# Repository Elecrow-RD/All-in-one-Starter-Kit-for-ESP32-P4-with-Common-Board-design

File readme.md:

### 1, Product picture

### 2, Product version number

|      | Hardware | Software | Remark |
| ---- | -------- | -------- | ------ |
| 1    | V1.0     | V1.0     | old |
| 2    | V1.1     | V1.1     | latest |

Differences between versions:

**V1.0**: This version uses a 360° servo.

**V1.1**: This version uses a 180° servo.

Use the corresponding code in Lesson 8.

### 3, product information

| Main Processor（ESP32-P4）       |                                                              |
| -------------------------------- | ------------------------------------------------------------ |
| CPU/SoC                          | 32-bit RISC-V dual-core processor up to 360 MHz for HP system;32-bit RISC-V single-core processor up to 40 MHz for LP system |
| System Memory                    | 16 MB (OPI/HPI)³  in-Package PSRAM                           |
| Storage                          | 128 KB HP ROM、16 KB LP ROM                                  |
| Development language             | C/C++ Language                                               |
| **Display**                      |                                                              |
| Size                             | 7inch                                                        |
| Resolution                       | 1024*600                                                     |
| Touch Type                       | Capacitive                                                   |
| Panel Type                       | IPS                                                          |
| **Wireless Communication**       |                                                              |
| Bluetooth                        | Not supported                                                |
| WiFi                             | Not supported                                                |
| Wireless communication expansion | Support can be used with [wireless module](https://www.elecrow.com/wireless-module-for-crowpanel-advanced-series.html) |
| Camera                           | 2 MegaPixels,100° wide-angle                                 |
| **Hardware**                     |                                                              |
| Interface                        | 1x TYPE-C Interface,1x I/C(ZX-HY2.0-4PZZ), 1x UART(ZX-HY2.0-4PZZ), 1xI/O(20P*2,P=2.54mm), 1xCSI, 1xUSB, 1x Ethernet,1x TF Card Slot |
| Button                           | Rest Button                                                  |
| LED Indicator                    | I/O port working status indicator light                      |
| **Other**                        |                                                              |
| Size                             | 195\*170*46（mm）                                            |
| Material                         | PP Plastic                                                   |
| Input                            | 5v                                                           |
| Weight                           | 600g                                                         |

### 4, Use the driver module

| Name | dependency library |
| ---- | ------------------ |
| LVGL | lvgl/lvgl@8.3.3    |

### 5,Quick Start
##### Arduino IDE starts

1.Download the library files used by this product to the 'libraries' folder.

C:\Users\Documents\Arduino\libraries\

2.Open the Arduino IDE

3.Open the code configuration environment and burn it

##### ESP-IDF starts

1.Right-click on an empty space in the project folder and select "Open with VS Code" to open the project.

2.In the IDF plug-in, select the port, then compile and flash

### 6,Folder structure.
|--3D file： Contains 3D model files (.stp) for the hardware. These files can be used for visualization, enclosure design, or integration into CAD software.

|--Datasheet: Includes datasheets for components used in the project, providing detailed specifications, electrical characteristics, and pin configurations.

|--Eagle_SCH&PCB: Contains **Eagle CAD** schematic (`.sch`) and PCB layout (`.brd`) files. These are used for circuit design and PCB manufacturing.

|--example: Provides example code and projects to demonstrate how to use the hardware and libraries. These examples help users get started quickly.

|--factory_firmware: Stores pre-compiled factory firmware that can be directly flashed onto the device. This ensures the device runs the default functionality.

|--factory_sourcecode:  Contains the source code for the factory firmware, allowing users to modify and rebuild the firmware as needed.

|--libraries: Includes necessary libraries required for compiling and running the project. These libraries provide drivers and additional functionalities for the hardware.

### 7,Pin definition
1，Ultrasonic Sensor：

2，LIGHT SENSOR

3，LED

4,Temperature & Humidity(DHT20)

5,DSI

6.PIR

IO24；

7.Servo Motor

IO25;

8,Accelerometer & Gyro

9,HALL SENSOR

IO7;

10,Custom key

IO16;

11,Touch Sensor

IO2;

12,MIC

13,Audio Interface

14,GAS-MQ2

IO17;

15,Relay

IO42;

16,CSI Interface

17,Wireless module

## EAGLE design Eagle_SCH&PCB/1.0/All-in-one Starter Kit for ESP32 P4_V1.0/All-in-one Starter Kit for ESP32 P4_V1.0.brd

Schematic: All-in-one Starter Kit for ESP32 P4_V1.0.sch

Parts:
C1, C2, C3, C10, C19, C20, C22, C25, C27, C28, C29, C32, C33, C34, C36, C38, C39, C41, C44, C46, C48, C49, C50, C51, C52, C56, C58, C60, C61, C63, C64, C66, C67, C69, C81, C85, C87, C89, C91, C95, C100, C102, C111, C118, C121, C209: 100nF; 0603
C4, C7: 15pF; 0603
C5, C6: 12pF; 0603
C8: 100nF_NC; 0603
C9, C11, C18, C21, C23, C24, C31, C42, C47, C65, C70, C75, C96, C97, C98, C109, C113, C122: 1uF; 0603
C12, C14, C15, C17, C26, C30, C35, C37, C55, C57, C59, C80, C86, C88, C94, C99, C103, C106, C110, C114, C115, C116: 10uF; 0603
C13, C16: 22pF; 0603
C40, C43: 10nF; 0603
C45, C195, C213: 4.7uF; 0603
C53, C54: 15pF; C0603
C62, C68, C83: 1uF; C0603
C71, C72, C76, C77: 47uF; 0603
C73, C74, C78, C79: 1nF; 0603
C82, C84, C90, C92: 22uF; C0805
C93: 10nF/25V; 0603
C101, C107, C108: 10nF; C0603
C104, C105: 22nF; C0603
C112: 1uF_NC; 0603
C117, C119, C120: 10uF; C0603
C212: 12pF; C0603
C225: 47uF; C0805
D001, D003: NC/H5VL10B; H5VL10B
D002, D019, D063, D064, D065: LESD5D5.0CT1G; TVS_LESD5D5.0CT1G
D004, D007: H5VL10B
D005: 1N4148; D_SOD123
D006: YELLOW; LED-8MM
D008: GREEN; LED-8MM
D009: BLUE; LED-8MM
D010, D021: DSS34_NC; D_SOD123FL
D11: RED; LED-8MM
D012, D013, D014, D015, D017, D018: LMBR140ET1G
D016: MM1W18_18V; LMSZ5233BT1G
D020: LMSZ5233BT1G_-6V; LMSZ5233BT1G
D022: B5819W; SOD-123_MINI-SMA
D023, D024, D025, D026, D027, D028, D029, D030, D031, D032, D033, D034, D035, D036, D037, D038, D039, D040, D041, D042, D043, D044, D045, D046, D047, D048, D049, D050, D051, D052, D053, D054, D055, D056, D057, D058, D059, D060, D061, D062: GREEN; LED_0603_SMT
D066: DSS34; D_SOD123FL
D130: RED; LED_0603_SMT
FB1: 0R/800mA; L0603
FB2, FB3, FB4, FB5: 1K/磁珠; L0603
FB9: FB 220R/MH2012HM221-T; L0805
IC1: W25Q128JVSIQ; SOIC127P790X216-8N
J1: USB2 High Speed & Power in; WZ3532R024-ESP32-V0.1-20221226_KEVIN_3.0TYPEC-SMD
J2: HR913550A; LORA_BASIC_GATEWAY_-MODULE_HR911105A-RJ45
J3: A_XBJ_CONNECTOR_TWIG-4P-2.0-SMD-FEMALE-REINFORCE9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; A_XBJ_CONNECTOR_4P-SMD-2.0-90D
J4: C42605_USB-TypeA; C42605/USB2.0
J5: USB1 & Power in; WZ3532R024-ESP32-V0.1-20221226_KEVIN_3.0TYPEC-SMD
J6: Gas Sensor Socket; MQ2
J7: HOLDER-MICROSD-9P; 9P-SMD-W/-RING
J8, J9: CONN_20; 1X20
J10, J18, J19: TWIG_2.0; 2.0_1X4
J11: L; 1X02L
J12: C262349_15P_1MM_下接_AFA07-S15FCC-00
J13, J16: HEADER-7P-18.28X2.5; H7-2.54-18.28X2.5X5MM
J14: CROWPI_POW_ULTRA
J15: R; 1X02L
J17: C19273935_40P_0.5MM_下接_HC-FPC-0.5-40P-FH20
J20: CON-2.54MM-3P; CON-PZ-2.54MM-1*3P-WT
J21, J22: CONN_01_3.1MM_SMD1X01_3.1MM_SMD; 1X01_2MM
J23, J24: CONN_01_2.6MM1X01_2.6-4MM; 1X01_2.6MM
J101: D203S_C78793; 3P-D8.1MM
J123: 3.5MM3P; 3.5MM*3P
K1, K2: KEY-4.5X4.5; KEY-4.5X4.5-SMD
K4: RELAY-SRD; REY5-6-19.1X15.5X15.3MM
K5, K6, K7, K8: BUTTON_2P
L1, L2: 2.2μH_C5832372; 1008(2520)
L3: NC; L0603
L4, L5, L6: 4.7uH_C45385206_2.4A; 1008(2520)
L7: 10UH; SMD-4X4MM
LED1, LED6: RED; DISCRETE_LED-0603
P1, P2, P3, P4, P5, P6, P7, P8, P9, P10, P11, P12, P13, P14, P15, P16, P17, P18, P19, P20, P21, P22, P23, P24, P25, P26, P27, P28, P29, P30, P31, P32, P33, P34, P35, P36, P37, P38, P39, P40, P41, P42, P43, P44, P45, P46, P47, P48, P49, P50, P51, P52, P54, P55, P56, P57, P58, P59, P60, P61, P62, P63, P64, P65, P66, P67, P68, P69, P70, P71: TEST_PADPAD-1.5MM; TEST_PAD-1.5MM
P101: KEY; 1P-D450
Q1, Q3, Q7: AO3401A; SOT23-3
Q2, Q4: LMBT3906DW1T1G
Q5, Q6, Q106, Q107: BSS138; SOT23
Q115: S9013; SOT23@1
Q405: 2N7002; SOT23
R1, R4, R7, R10, R61, R64, R73, R79, R81, R83, R123: 5.1K; R0603
R2, R3, R5, R8, R9, R15, R17, R19, R20, R30, R31, R34, R35, R37, R39, R40, R41, R42, R43, R44, R45, R46, R47, R48, R49, R50, R51, R52, R53, R54, R55, R58, R59, R60, R63, R68, R69, R70, R71, R74, R75, R76, R77, R78, R88, R118, R119, R120, R133, R140, R141, R144, R145, R151, R176, R185, R186, R187, R188, R189, R190, R196, R197, R199, R200, R203, R205, R206, R211, R212, R213, R214, R215, R216, R217, R219, R220, R221, R222, R225, R227, R228, R230, R231, R232, R289, R290, R291, R292, R293, R294, R295, R296, R297, R298, R302, R305, R311, R312, R313, R315, R317, R324, R328, R332: 0R; R0603
R6: 10M_NC; R0603
R11, R12, R276: 22R; R0603
R13, R14, R16, R18, R22, R24, R25, R38, R94, R95, R107, R109, R112, R113, R115, R117, R146, R149, R161, R162, R164, R177, R178, R179, R182, R191, R194, R201, R237, R273, R283, R286, R288: 10K; R0603
R21, R23, R173, R175: 51K; R0603
R26, R165, R284: 100K; R0603
R27: 22.1K; R0603
R28: 0R/0805; R0805-SP
R29: 13k; R0603
R32, R33, R86, R87, R147, R180, R181, R192, R193, R210, R238: 10K_NC; R0603
R36, R91, R134, R198, R226, R258, R260, R329: 0R_NC; R0603
R56, R62, R92, R106, R169, R209, R287, R639, R652: 1K; R0603
R57, R108, R110: 1M; R0603
R65: 6.2K; R0603
R66: 1.5K_NC; R0603
R67: 1.5K; R0603
R72, R80, R82, R84, R85: 5.1K_NC; R0603
R89, R97, R98, R121, R122, R125, R126, R207, R208, R257, R259, R422, R423: 4.7K; R0603
R90: 0R; R0805-SP
R93, R99, R102: 470R; R0603
R96, R148, R152, R153, R154, R155, R156, R157, R274: 100R; R0603
R100, R101, R223, R224: 4.7K; R0603-SP
R103, R104: 4.7K_NC; R0603
R105: 500K; 3P-SMD-SQUA-3.6X3.3
R111: 1M_1%; R0603
R114: 3.3K; R0603
R116: 130K; R0603
R124: 5.1R; R0603
R127, R128, R129, R131, R132, R160: 10K; R0603-SP
R130: 10K_NC; R0603-SP
R135, R139: 100K; R0603-SP
R136, R137, R138, R170, R171: 0R; R0603-SP
R142: 95.3K; R0603
R143: 50K; R0603-SP
R150: 13K; R0603
R158, R202: 4.02K; R0603
R159: 1.1R; R0603-SP
R163: 1.1R_NC; R0603-SP
R166: 180K; R0603
R167: 12K; R0603
R168: 1.6K; R0603
R172, R174: 220R; R0603
R195: 1K_NC; R0603
R234, R235, R236, R239, R240, R241, R242, R243, R244, R245, R246, R247, R248, R249, R250, R251, R252, R253, R254, R255, R256, R261, R262, R263, R264, R265, R266, R267, R268, R269, R270, R271, R272, R275, R277, R278, R279, R280, R281, R282, R285: 30K; R0603
R299, R307, R653: 2K; R0603
R654: 3.6K; R0603
R655: 8.2K; R0603
SW1, SW2: switch_6pin; SWITCH_6PIN_2P
TP1, TP2, TP3, TP4, TP5, TP6, TP7, TP8, TP9, TP10, TP11, TP12: TPTP08R; TP08R
U1: ESP32-P4NRW32; IC_ESP32-P4NRW32
U2, U3: RY3430_C370755; SOT95P280X145-5N
U4: IP101GR; QFN32_4X4
U5: DHT20; CROWTAIL-DHT20-V1.0-20211013_DHT20
U6: LSM6DS3TR-C; LGA-14L
U7: HAL248; SOT-23W
U8: LMD4737T261; MIC_LMD4737T261
U9: NS4168-L; NS4168-ESOP-8
U10: NS4168-R; NS4168-ESOP-8
U11: MT9201; COOPER_SOT23-6
U12: CH340K; ESOP-10-EP-150MIL
U13: UMH3NTN; SOP65P210X100-6N
U14: WS2814A
U15: ME6211C18M5G-N_NC; SOT95P282X145-5N
U16: SX1308; SOT95P280X145-6N
U17: MT3540; SOT95P280X145-5N
U18: MT3608; DBV_R-PDSO-G6
U19: SGM3799_NC; IC_SGM3799_TQFN2.6X1.8_16L
U44: ETA6280S2F/RY2121; IC_SOT23-5
U101: BIS0001; SOP16
U121: BH1750; B1750
U123: TTP223; SOT23-6L
U$196: MSOP10
Y1: 40MHZ; X322540MPB4SI
Y2: X322525MSB4SI; SMD3225
Y4: 32.768K; NORDIC_NRF_XTAL_3215_N

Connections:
3.3V: J17.2, P34.P$1, R199.2
3V3_MIC: C69.2, FB1.2, R133.1, U8.6 (VDD_6)
+5V_SYS_GAS: C67.2, J6.1 (A), J6.2 (H), J6.3 (A), R126.2, SW1.2 (2_COM2)
AUDIO_VDD_3V3: Q7.3 (3_D), R135.2, R139.2
AVDD33: C55.2, C56.2, R59.1, U4.31 (AVDD33)
BIT_P0.31_HAL: C65.1, P21.P$1, R123.1, R213.1, U7.2 (VOUT)
CLK_N: R186.2, U1.37 (DSI_CLKN)
CLK_P: R185.2, U1.38 (DSI_CLKP)
COL: R79.1, R80.2, U4.4 (COL/RMII)
COM: J123.2, K4.2
CRS: R81.1, R82.2, U4.20 (CRS/LEDMOD)
CSICLK_N: R156.1, U1.45 (CSI_CLKN)
CSICLK_P: R157.1, U1.44 (CSI_CLKP)
CSID0_N: R152.1, U1.42 (CSI_DATAN0)
CSID0_P: R153.1, U1.43 (CSI_DATAP0)
CSID1_N: R154.1, U1.46 (CSI_DATAN1)
CSID1_P: R155.1, U1.47 (CSI_DATAP1)
CSI_3V3: C80.1, C81.1, R144.2, R145.1, R146.1, R147.1
CSI_CLK_N: J12.8, R156.2, TP5.TP
CSI_CLK_P: J12.9, R157.2, TP6.TP
CSI_D0_N: J12.2, R152.2, TP1.TP
CSI_D0_P: J12.3, R153.2, TP2.TP
CSI_D1_N: J12.5, R154.2, TP3.TP
CSI_D1_P: J12.6, R155.2, TP4.TP
DA1: J7.8 (DATA1), P49.P$1, R127.1
DA2: J7.1 (DATA2), P51.P$1, R131.1
DATA0_N: R190.2, U1.40 (DSI_DATAN0)
DATA0_P: R189.2, U1.39 (DSI_DATAP0)
DATA1_N: R188.2, U1.36 (DSI_DATAN1)
DATA1_P: R187.2, U1.35 (DSI_DATAP1)
DN_N: D019.2, J5.A7 (DN1), J5.B7 (DN2), R9.2
DP_P: D064.2, J5.A6 (DP1), J5.B6 (DP2), R8.2
DSI_CLK_N: J17.23, R186.1, TP11.TP
DSI_CLK_P: J17.24, R185.1, TP12.TP
DSI_DATA0_N: J17.17, R190.1, TP7.TP
DSI_DATA0_P: J17.18, R189.1, TP8.TP
DSI_DATA1_N: J17.20, R188.1, TP9.TP
DSI_DATA1_P: J17.21, R187.1, TP10.TP
DTR: R13.2, U12.4 (DTR#), U13.4 (E2)
EN_DCDC: R31.2, U1.79 (EN_DCDC)
ESP_LDO_VO1: C21.2, R37.2, U1.71 (VFB1/VO1)
ESP_LDO_VO2: C24.1, R40.2, U1.72 (VFB2/VO2)
ESP_LDO_VO3: C47.2, R51.2, U1.73 (VFB3/VO3)
ESP_LDO_VO4: C31.2, R44.2, U1.74 (VFB4/VO4)
ESP_VDD_HP_1V2: R34.2, R48.2, R49.2, R50.2
FB_DCDC: C16.1, R32.2, R33.1, R203.1, U3.5 (FB)
FLASH_CK: IC1.6 (CLK), U1.32 (FLASH_CK)
FLASH_CS: IC1.1 (/CS), R38.1, U1.27 (FLASH_CS)
FLASH_D: IC1.5 (DI_(IO0)), U1.33 (FLASH_D)
FLASH_HOLD: IC1.7 (/HOLD_OR_/RESET_(IO3)), U1.31 (FLASH_HOLD)
FLASH_Q: IC1.2 (DO_(IO1)), U1.28 (FLASH_Q)
FLASH_WP: IC1.3 (/WP_(IO2)), U1.29 (FLASH_WP)
GND: C1.2, C2.1, C3.2, C4.2, C5.2, C6.2, C7.1, C8.2, C9.1, C10.1, C11.1, C12.2, C14.1, C15.2, C17.1, C18.2, C19.1, C20.2, C21.1, C22.2, C23.2, C24.2, C25.2, C26.1, C27.2, C28.2, C29.2, C30.1, C31.1, C32.2, C33.2, C34.2, C35.1, C36.2, C37.1, C38.2, C39.2, C40.2, C41.2, C42.2, C43.2, C44.2, C45.2, C46.2, C47.1, C48.2, C49.2, C50.1, C51.1, C52.1, C53.2, C54.1, C55.1, C56.1, C57.1, C58.1, C59.1, C60.1, C61.1, C62.1, C63.1, C64.1, C65.2, C66.1, C67.1, C68.1, C69.1, C70.2, C71.2, C72.2, C73.1, C74.1, C75.2, C76.2, C77.2, C78.1, C79.1, C80.2, C81.2, C82.2, C83.1, C84.2, C85.1, C86.2, C87.2, C88.2, C89.2, C90.2, C91.2, C92.2, C94.2, C95.2, C98.2, C99.2, C100.2, C101.1, C102.1, C106.1, C107.2, C108.2, C109.2, C110.2, C111.2, C112.2, C113.2, C114.1, C115.2, C116.2, C117.1, C118.1, C119.1, C120.1, C121.1, C122.1, C195.2, C209.1, C212.1, C213.1, C225.1, D001.1, D002.1, D003.1, D004.2, D007.2, D016.2, D018.1, D019.1, D020.1, D063.1, D064.1, D065.1, IC1.4 (GND), J1.A1 (GND), J1.A12 (GND), J1.B1 (GND), J1.B12 (GND), J1.P$9, J1.P$10, J1.P$11, J1.P$12, J3.4, J3.SS1, J3.SS2, J4.1 (1.GND), J4.5, J4.6, J5.A1 (GND), J5.A12 (GND), J5.B1 (GND), J5.B12 (GND), J5.P$9, J5.P$10, J5.P$11, J5.P$12, J7.6 (VSS), J7.G1, J7.G2, J7.G3, J7.G4, J8.4, J8.5, J8.6, J8.13, J8.17, J8.20, J9.16, J9.17, J9.20, J10.1, J11.3, J11.4, J12.1, J12.4, J12.7, J12.10, J12.16, J12.17, J13.6, J13.6-6 (6), J14.P$1 (1_GND), J15.3, J15.4, J17.3, J17.7, J17.8, J17.9, J17.10, J17.16, J17.19, J17.22, J17.25, J17.28, J17.31, J17.41, J17.42, J18.1, J19.1, J20.3 (S), J21.1, J22.1, J23.1, J24.1, J101.3 (G), K1.1, K2.2, K5.P$1, K6.P$1, K7.P$1, K8.P$1, LED6.-, P20.P$1, P28.P$1, P29.P$1, P31.P$1, P65.P$1, Q115.2 (E), R1.2, R4.1, R7.2, R10.1, R21.1, R22.1, R23.1, R24.1, R27.2, R29.2, R33.2, R57.1, R62.2, R64.2, R65.2, R73.1, R80.1, R82.1, R84.1, R87.1, R91.1, R107.1, R108.1, R119.1, R120.1, R124.1, R125.2, R132.2, R134.1, R143.1, R150.2, R158.2, R159.1, R160.2, R162.1, R163.1, R167.1, R169.1, R173.1, R175.1, R180.1, R182.1, R192.1, R194.1, R202.1, R234.2, R238.1, R252.2, R256.2, R261.2, R262.2, R263.2, R264.2, R265.2, R266.2, R267.2, R268.2, R269.2, R270.2, R271.2, R272.2, R273.1, R275.2, R277.2, R278.2, R279.2, R280.2, R281.2, R282.2, R285.1, R286.2, R288.2, R307.2, SW2.4 (4_1A), U1.105 (GND), U2.2 (GND), U3.2 (GND), U4.EXP (PAD), U5.3 (GND), U6.6 (GND), U6.7 (GND), U7.3 (GND), U8.1 (GND_1), U8.3 (GND_3), U9.7 (GND), U9.9 (PE), U10.7 (GND), U10.9 (PE), U11.2 (2-GND), U12.3 (GND), U12.EP, U14.4 (GND), U15.2 (VSS), U16.2 (2_GND), U17.2 (2_GND), U18.2 (GND), U19.6 (6_GND), U44.2 (2_GND), U101.7 (VSS), U121.3 (GND\), U123.2 (GND), U$196.5 (GND), Y1.2 (GND_1), Y1.4 (GND_2), Y2.2 (GND), Y2.4 (GND)
IN1: C212.2, P101.1, U123.3 (IN)
INT1: P22.P$1, U6.4 (INT1)
INT2: P23.P$1, U6.9 (INT2)
INT_TP: J17.4, P35.P$1, R227.2
IO2: U1.2 (GPIO2), U19.4 (4_COM2), U$196.3 (CO+)
IO2_CLK: J16.3, J16.3-3 (3), P45.P$1, R177.1, U19.3 (3_NO2), U$196.9 (L1+)
IO2_RTS: P18.P$1, R287.2, U19.5 (5_NC2), U$196.7 (L0+)
IO3_MIC_CLK: U1.3 (GPIO3), U8.4 (CLK_4)
IO4_MIC_DATA: U1.4 (GPIO4), U8.5 (DATA_5)
IO5_RESET_LCD: R151.1, R231.2, U1.5 (GPIO5)
IO6_AUDIO_EN: Q7.1 (1_G), R95.1, R294.1, U1.6 (GPIO6)
IO7: R315.2, U1.7 (GPIO7), U19.8 (8_COM3), U$196.4 (CO-)
IO7_CMD: J16.2, J16.2-2 (2), P44.P$1, R178.1, U19.7 (7_NO3), U$196.8 (L1-)
IO7_HALL: R213.2, U19.9 (9_NC3), U$196.6 (L0-)
IO8_LED: P32.P$1, R148.1, R290.2, U1.8 (GPIO8)
IO9: R220.2, R291.2, U1.10 (GPIO9)
IO9_W_CLK: J13.2, J13.2-2 (2), P27.P$1, R220.1
IO10: R221.2, R295.2, U1.11 (GPIO10)
IO10_W_MISO: J13.3, J13.3-3 (3), P26.P$1, R221.1
IO11: R222.2, R296.2, U1.12 (GPIO11)
IO11_W_MOSI: J13.4, J13.4-4 (4), P25.P$1, R222.1
IO12_US_ECHO: R299.2, U1.13 (GPIO12)
IO13_US_TRIG: R212.2, U1.14 (GPIO13)
IO14: R219.2, R324.2, U1.15 (GPIO14)
IO14_W_BUSY: J16.6, J16.6-6 (6), P40.P$1, R219.1
IO15: R5.2, R302.1, U1.16 (GPIO15)
IO15_W: J16.5, J16.5-5 (5), P41.P$1, R5.1
IO16_ADC_KEY: P16.P$1, R214.2, R639.2, R652.2, R653.2, R654.2, R655.2
IO17_ADC_MQ2: J6.4 (B), J6.6 (B), P17.P$1, R125.1, R215.2
IO18_I2C1_SDA: J17.5, P36.P$1, Q107.2 (S), R103.2, R205.2, R208.2, R260.1, U5.2 (SDA), U6.14 (SDA), U121.4 (SDA)
IO18_SDA: J10.3, J18.3, Q107.3 (D), R259.2, R260.2
IO19_I2C1_SCL: J17.6, P37.P$1, Q106.2 (S), R104.2, R206.2, R207.2, R258.1, U5.4 (SCL), U6.13 (SCL), U121.6 (SCL)
IO19_SCL: J10.4, J18.4, Q106.3 (D), R257.2, R258.2
IO20_LED_BK_EN: R160.1, R232.2, U11.4 (4-EN)
IO21_I2S_LRCLK: R136.2, U1.23 (GPIO21)
IO22_I2S_BCLK: R137.2, U1.24 (GPIO22)
IO23_I2S_DSDIN: R138.2, U1.25 (GPIO23)
IO24_PIR: P30.P$1, R112.1, U1.52 (GPIO24)
IO25_SERVO: Q405.2 (S), R211.2, R329.2, R422.1
IO32_UPDN: R230.1, U1.63 (GPIO32)
IO33_SHLR: R225.1, U1.64 (GPIO33)
IO35_BOOT: C8.1, K2.1, R17.1, R18.1, R70.2, U13.3 (C2)
IO36: R94.2, U1.68 (GPIO36)
IO39_SD_DO: J7.7 (DO), P6.P$1, R128.1, R332.2
IO40_RESET_TP: R228.1, U1.81 (GPIO40)
IO41_INT_TP: R227.1, R317.2, U1.82 (GPIO41)
IO42_RELAY: P58.P$1, R274.2, U1.83 (GPIO42)
IO43_SD_SCK: J7.5 (SCLK), P7.P$1, R217.2
IO44_SD_CMD: J7.3 (DI), P8.P$1, R129.1, R216.2
IO45_I2C2_SDA: J12.14, P69.P$1, R98.2, R313.2, U1.87 (GPIO45)
IO46_I2C2_SCL: J12.13, P68.P$1, R97.2, R312.2, U1.88 (GPIO46)
IO47_TX: J19.3, Q5.3 (D), R223.2
IO47_UART_TX: Q5.2 (S), R224.2, R297.2, U1.89 (GPIO47)
IO48_RX: J19.4, Q6.3 (D), R101.2
IO48_UART_RX: Q6.2 (S), R100.2, R298.2, U1.90 (GPIO48)
IO53_W_TX_CE: R171.2, R328.2, U1.97 (GPIO53)
IO54_W_RX_IRQ: R170.2, R305.1, U1.98 (GPIO54)
IO-5: J9.13, R231.1, R247.2
IO-6: J9.12, R246.2, R294.2
IO-7: J9.10, R244.2, R315.1
IO-8: J9.11, R245.2, R290.1
IO-9: J9.6, R240.2, R291.1
IO-10: J9.5, R239.2, R295.1
IO-11: J9.4, R236.2, R296.1
IO-14: J9.3, R235.2, R324.1
IO-15: J9.9, R243.2, R302.2
IO-26: J9.15, R249.2, R293.2
IO-27: J9.14, R248.2, R292.2
IO-41: J8.14, R253.2, R317.1
IO-45: J8.18, R254.2, R313.1
IO-46: J8.19, R255.2, R312.1
IO-47: J9.18, R250.2, R297.1
IO-48: J9.19, R251.2, R298.1
IO-53: J9.7, R241.2, R328.1
IO-54: J9.8, R242.2, R305.2
IOT_5V: J13.7, J13.7-7 (7), L3.1
IO_DO_N: R12.1, U1.69 (GPIO37)
IO_DO_P: R11.1, U1.70 (GPIO38)
LCD_3V3: R195.2, R199.1, R200.2, R201.2
LCD_AVDD_9V6: C92.1, C93.1, D013.1, D014.2, J17.32, P14.P$1, R166.2, R168.2
LCD_VCOM_3V3: C94.1, C95.1, P15.P$1, R168.1, R169.2, R197.1, R198.1
LCD_VDD_1V8: C88.1, C89.1, P10.P$1, R141.2, R179.2, R181.2, R191.2, R193.2, R196.1, U15.5 (VOUT)
LCD_VGH_18V: C99.1, C100.1, D016.1, J17.38, P12.P$1, R172.1, R173.2
LCD_VGL_-6V: C110.1, C111.1, D020.2, J17.37, P11.P$1, R174.1, R175.2
LED+: C84.1, C85.2, D010.-, D012.1, P63.P$1, R176.1, U11.5 (5-OV)
LED-: J17.33, J17.34, P64.P$1, R159.2, R163.2, U11.3 (3-FB)
unnamed: Q3.1 (1_G), Q4.3 (C1), R23.2
unnamed: C6.1, R6.1, U1.1 (GPIO1), Y4.2
unnamed: C5.1, R6.2, U1.104 (GPIO0), Y4.1
unnamed: Q1.1 (1_G), Q2.3 (C1), R21.2
unnamed: Q2.2 (B2), Q2.5 (B1), Q2.6 (C2), R22.2
unnamed: C43.1, C44.1, C45.1, C46.1, R52.1, U1.51 (VCCA)
unnamed: Q4.2 (B2), Q4.5 (B1), Q4.6 (C2), R24.2
unnamed: J1.B5 (CC2), R4.2
unnamed: J1.A5 (CC1), R1.1
unnamed: J5.A5 (CC1), R7.1
unnamed: R12.2, U12.9 (RXD)
unnamed: R11.2, U12.8 (TXD)
unnamed: R13.1, U13.2 (B1)
unnamed: R15.1, U1.103 (CHIP_PU)
unnamed: R14.1, U13.5 (B2)
unnamed: R17.2, U1.66 (GPIO35)
unnamed: D130.2 (2_K), R307.1
unnamed: R209.1, U44.4 (4_EN)
unnamed: J2.12 (YLED+), R55.1
unnamed: R25.1, U2.1 (EN)
unnamed: L1.1, U2.3 (SW)
unnamed: C13.2, C14.2, L1.2, P2.P$1, R26.1, R28.1
unnamed: C13.1, R26.2, R27.1, U2.5 (FB)
unnamed: R31.1, R210.2, U3.1 (EN)
unnamed: L2.1, U3.3 (SW)
unnamed: C16.2, C17.2, L2.2, P3.P$1, R32.1, R34.1
unnamed: R203.2, U1.78 (FB_DCDC)
unnamed: C15.1, R35.1, R210.1, U3.4 (VIN)
unnamed: C32.1, R45.1, U1.96 (VDDPST_6)
unnamed: J2.11 (YLED-), R56.1
unnamed: J2.7 (NC1), J2.8 (NC2), J2.M1 (SHIELD1), J2.M2 (SHIELD2), R57.2
unnamed: C50.2, J2.4 (TCT)
unnamed: R74.2, U1.92 (GPIO49)
unnamed: C51.2, J2.5 (RCT)
unnamed: R75.2, U1.93 (GPIO50)
unnamed: R77.2, U1.58 (GPIO29)
unnamed: R85.1, U4.24 (TEST_ON)
unnamed: R76.2, U1.60 (GPIO30)
unnamed: R71.2, U1.65 (GPIO34)
unnamed: R78.2, U1.57 (GPIO28)
unnamed: R88.2, U1.94 (GPIO51)
unnamed: J2.10 (GLED-), R62.1
unnamed: J2.9 (GLED+), R63.1
unnamed: R68.2, U1.61 (GPIO31)
unnamed: LED1.+, R89.1
unnamed: J14.P$3 (3_TRIG), R212.1
unnamed: R232.1, U1.22 (GPIO20)
unnamed: R214.1, U1.17 (GPIO16)
unnamed: C209.2, R113.1, U121.5 (DVI)
unnamed: R91.2, U14.5 (5_DOUT)
unnamed: R69.2, U1.95 (GPIO52)
unnamed: D009.2 (C), U14.3 (3_OUTB)
unnamed: D11.1 (A), R93.2
unnamed: R65.1, U4.25 (ISET)
unnamed: D008.2 (C), U14.2 (2_OUTG)
unnamed: D11.2 (C), U14.1 (1_OUTR)
unnamed: R29.1, U44.3 (3_SET)
unnamed: D006.1 (A), R96.2
unnamed: J5.B5 (CC2), R10.2
unnamed: D006.2 (C), U14.8 (8_OUTW)
unnamed: R142.2, R150.1, U18.3 (FB)
unnamed: D008.1 (A), R99.2
unnamed: R92.2, U14.7 (7_VDD)
unnamed: D022.A, L7.2, U18.1 (SW)
unnamed: D009.1 (A), R102.2
unnamed: R117.1, U101.3 (RR1)
unnamed: C108.1, R117.2, U101.4 (RC1)
unnamed: R112.2, U101.2 (VO)
unnamed: R110.2, U101.6 (RR2)
unnamed: C107.1, R110.1, U101.5 (RC2)
unnamed: C104.2, R105.2 (3), R105.3 (2), U101.12 (2OUT)
unnamed: C104.1, R106.2, R116.2, U101.13 (2IN-)
unnamed: R109.2, U101.9 (VC)
unnamed: R108.2, U101.10 (IB)
unnamed: C101.2, J101.2 (S), R107.2, R118.2
unnamed: C103.2, C105.1, R111.1, U101.16 (1OUT)
unnamed: C105.2, R111.2, R114.2, U101.15 (1IN-)
unnamed: C103.1, R106.1
unnamed: C225.2, R114.1
unnamed: R115.2, U101.1 (A)
unnamed: R118.1, U101.14 (1IN+)
unnamed: R105.1, R116.1
unnamed: R119.2, U6.2 (SDX)
unnamed: R120.2, U6.3 (SCX)
unnamed: R121.2, U6.12 (CS)
unnamed: R122.2, U6.1 (SDO)
unnamed: J6.5 (H), R124.2
unnamed: LED6.+, R126.1
unnamed: R217.1, U1.84 (GPIO43)
unnamed: R216.1, U1.86 (GPIO44)
unnamed: R133.2, R134.2, U8.2 (L/R_2)
unnamed: R135.1, U10.1 (CTRL)
unnamed: P61.P$1, R136.1, U9.2 (LRCLK), U10.2 (LRCLK)
unnamed: P60.P$1, R137.1, U9.3 (BCLK), U10.3 (BCLK)
unnamed: P59.P$1, R138.1, U9.4 (SDATA), U10.4 (SDATA)
unnamed: FB2.1, U10.8 (VOP)
unnamed: FB3.1, U10.5 (VON)
unnamed: R332.1, U1.80 (GPIO39)
unnamed: C78.2, FB4.2, J11.2, P54.P$1
unnamed: R139.1, R143.2, U9.1 (CTRL)
unnamed: C97.2, D017.1, D018.2
unnamed: R162.2, U$196.10 (EN)
unnamed: FB4.1, U9.8 (VOP)
unnamed: FB5.1, U9.5 (VON)
unnamed: C79.2, FB5.2, J11.1, P55.P$1
unnamed: C74.2, FB3.2, J15.1, P57.P$1
unnamed: J12.15, P70.P$1, R145.2
unnamed: J12.11, P66.P$1, R146.2
unnamed: J12.12, P67.P$1, R147.2
unnamed: R158.1, U1.48 (CSI_REXT)
unnamed: D010.+, D012.2, L5.2, U11.1 (1-SW)
unnamed: C96.1, C97.1, D013.2, L4.2, U16.1 (1_SW)
unnamed: R164.2, U15.3 (CE)
unnamed: R165.2, U16.4 (4_EN)
unnamed: C96.2, D014.1, D015.2
unnamed: C93.2, R166.1, R167.2, U16.3 (3_FB)
unnamed: J13.1, J13.1-1 (1), P43.P$1, R171.1
unnamed: J16.1, J16.1-1 (1), P42.P$1, R170.1
unnamed: C98.1, D015.1, R172.2
unnamed: C109.1, D017.2, R174.2
unnamed: J17.39, J17.40, R176.2
unnamed: R205.1, U1.19 (GPIO18)
unnamed: R206.1, U1.20 (GPIO19)
unnamed: C73.2, FB2.2, J15.2, P56.P$1
unnamed: R211.1, U1.53 (GPIO25)
unnamed: J17.12, J17.13, R196.2, R198.2
unnamed: J17.11, R197.2
unnamed: R202.2, U1.34 (DSI_REXT)
unnamed: R215.1, U1.18 (GPIO17)
unnamed: D023.2 (2_K), R234.1
unnamed: D024.2 (2_K), R235.1
unnamed: D025.2 (2_K), R236.1
unnamed: D026.2 (2_K), R239.1
unnamed: D027.2 (2_K), R240.1
unnamed: K8.P$2, R652.1
unnamed: D028.2 (2_K), R241.1
unnamed: K7.P$2, R653.1
unnamed: K6.P$2, R654.1
unnamed: D029.2 (2_K), R242.1
unnamed: D030.2 (2_K), R243.1
unnamed: K5.P$2, R655.1
unnamed: D031.2 (2_K), R244.1
unnamed: D032.2 (2_K), R245.1
unnamed: D033.2 (2_K), R246.1
unnamed: D034.2 (2_K), R247.1
unnamed: D035.2 (2_K), R248.1
unnamed: D036.2 (2_K), R249.1
unnamed: D037.2 (2_K), R250.1
unnamed: D038.2 (2_K), R251.1
unnamed: D039.2 (2_K), R252.1
unnamed: D040.2 (2_K), R253.1
unnamed: D041.2 (2_K), R254.1
unnamed: D042.2 (2_K), R255.1
unnamed: D043.2 (2_K), R256.1
unnamed: D044.2 (2_K), R261.1
unnamed: D045.2 (2_K), R262.1
unnamed: D046.2 (2_K), R263.1
unnamed: D047.2 (2_K), R264.1
unnamed: D048.2 (2_K), R265.1
unnamed: D049.2 (2_K), R266.1
unnamed: D050.2 (2_K), R267.1
unnamed: D051.2 (2_K), R268.1
unnamed: D052.2 (2_K), R269.1
unnamed: D053.2 (2_K), R270.1
unnamed: D054.2 (2_K), R271.1
unnamed: D055.2 (2_K), R272.1
unnamed: D056.2 (2_K), R275.1
unnamed: D057.2 (2_K), R277.1
unnamed: D058.2 (2_K), R278.1
unnamed: D059.2 (2_K), R279.1
unnamed: D060.2 (2_K), R280.1
unnamed: D061.2 (2_K), R281.1
unnamed: D062.2 (2_K), R282.1
unnamed: R148.2, U14.6 (6_DIN)
unnamed: R149.2, U101.8 (!RESET)
unnamed: R283.2, U17.4 (4_EN)
unnamed: D066.+, L6.2, U17.1 (1_SW)
unnamed: J9.1, J9.2, R289.2
unnamed: R284.1, R285.2, U17.3 (3_FB)
unnamed: J8.1, J8.2, J8.3, R311.1
unnamed: R237.1, R238.2, U121.2 (ADDR)
unnamed: Q115.1 (B), R273.2, R274.1
unnamed: R288.1, U123.4 (AHLB), U123.6 (TOG)
unnamed: R286.1, R287.1, U123.1 (OUT)
unnamed: J14.P$2 (2_ECHO), R299.1
NC: J123.1, K4.4
NO: J123.3, K4.5
PHY_3V3: R55.2, R58.2, R59.2, R60.2, R61.2, R66.2, R67.2, R72.2, R79.2, R81.2, R83.2, R85.2, R86.2
PHY_AD0: R56.2, R61.1, U4.11 (LED0/PHY_AD0)
PHY_AD3: R63.2, R64.1, U4.12 (LED3/PHY_AD3)
PHY_CLK_IO50: R75.1, U4.10 (TXCLK/50M_CLKI), U4.14 (RXCLK/50M_CLKO)
PHY_MDC_IO31: R66.1, R68.1, U4.22 (MDC)
PHY_MDIO_IO52: R67.1, R69.1, U4.23 (MDIO)
PHY_RSTN_IO51: R86.1, R87.2, R88.1, U4.32 (RESET_N)
PHY_RXD0_IO29: R77.1, U4.18 (RXD0)
PHY_RXD1_IO30: R76.1, U4.17 (RXD1)
PHY_RXDV_IO28: R78.1, U4.19 (RXDV/CRS_DV)
PHY_TXD0_IO34: R71.1, U4.9 (TXD0)
PHY_TXD1_IO35: R70.1, U4.8 (TXD1)
PHY_TXEN_IO49: R74.1, U4.5 (TXEN)
REGOUT: C59.2, C60.2, U4.28 (REGOUT)
RESET_LCD: C112.1, J17.14, P38.P$1, R151.2, R193.1, R194.2, R195.1, R226.2
RESET_TP: C113.1, J17.1, P33.P$1, R201.1, R228.2
RST_EN: C3.1, K1.2, R15.2, R16.1, R226.1, U13.6 (C1)
RTS: R14.2, U12.6 (RTS#), U13.1 (E1)
RXER: R83.1, R84.2, U4.21 (RXER/INTR_32)
RX_N: J2.6 (RD-), U4.26 (MDI_RN)
RX_P: J2.3 (RD+), U4.27 (MDI_RP)
SDCS: J7.2 (CS), P50.P$1, R130.1, R132.1
SEL: P48.P$1, R161.1, SW2.5 (5_COM1), U19.2 (2_IN1_2), U19.10 (10_IN3_4), U$196.2 (SEL)
SERVO: J3.1, J20.1 (G), P71.P$1, Q405.3 (D), R329.1, R423.2
SHLR: J17.35, P46.P$1, R181.1, R182.2, R225.2
STBYB: J17.15, P39.P$1, R191.1, R192.2
TXER: R72.1, R73.2, U4.1 (TXER/FXSD)
TX_N: J2.2 (TD-), U4.29 (MDI_TN)
TX_P: J2.1 (TD+), U4.30 (MDI_TP)
UPDN: J17.36, P47.P$1, R179.1, R180.2, R230.2
USB1_5V: C9.2, D063.2, J5.A4 (VBUS), J5.A9 (VBUS), J5.B4 (VBUS), J5.B9 (VBUS), P4.P$1, Q1.3 (3_D), Q2.1 (E2)
USB1_D_N: R9.1, U12.2 (UD-)
USB1_D_P: R8.1, U12.1 (UD+)
USB2_5V: C11.2, D002.2, J1.A4 (VBUS), J1.A9 (VBUS), J1.B4 (VBUS), J1.B9 (VBUS), P5.P$1, Q3.3 (3_D), Q4.1 (E2)
USB2_D_N: D004.1, J1.A7 (DN1), J1.B7 (DN2), R3.2
USB2_D_P: D007.1, J1.A6 (DP1), J1.B6 (DP2), R2.2
USB2_N: D001.2, J4.3 (3.D-), R20.2
USB2_P: D003.2, J4.2 (2.D+), R19.2
USBD_N: R20.1, U1.49 (DM)
USBD_P: R19.1, U1.50 (DP)
USB_5V: C12.1, C106.2, L6.1, P1.P$1, Q1.2 (2_S), Q2.4 (E1), Q3.2 (2_S), Q4.4 (E1), R25.2, R90.1, R283.1, U2.4 (VIN), U17.5 (5_VIN)
USB_A_N: R3.1, R293.1, U1.55 (GPIO26)
USB_A_P: R2.1, R292.1, U1.56 (GPIO27)
V+: K4.1, R276.2
V-: D005.+, K4.3, LED1.-, Q115.3 (C)
VBAT: C49.1, C115.1, R54.1, U1.102 (VBAT)
VBUS_OUT: C116.1, D065.2, J4.4 (4.VCC), P9.P$1, U44.1 (1_OUT)
VCC_5V_SERVO: C119.2, C120.2, C121.2, D021.-, D022.C, J3.3, J20.2 (V), P52.P$1, R142.1, R423.1
VCC_RELAY: C61.2, D005.-, FB9.1, R89.2, R276.1
VDDA: C48.1, R53.1, U1.101 (VDDA)
VDDPST: C22.1, C23.1, R40.1, U1.59 (VDDPST), U1.67 (VDDPST)
VDDPST_1: C25.1, C26.2, R41.1, U1.9 (VDDPST_1)
VDDPST_2: C27.1, R42.1, U1.21 (VDDPST_2)
VDDPST_3: C18.1, C19.2, R36.1, R37.1, R39.1, U1.30 (VDDPST_3)
VDDPST_4: C28.1, R43.1, U1.62 (VDDPST_4)
VDDPST_5: C29.1, C30.2, R44.1, U1.85 (VDDPST_5)
VDDPST_DCDC: C34.1, C35.2, R47.1, U1.77 (VDDPST_DCDC)
VDDPST_LDO: C33.1, R46.1, U1.75 (VDDPST_LDO)
VDD_3V3: C1.1, C2.2, C62.2, C63.2, C64.2, C66.2, C68.2, C70.1, C71.1, C72.1, C75.1, C76.1, C77.1, C102.2, C122.2, C213.2, D023.1 (1_A), D024.1 (1_A), D025.1 (1_A), D026.1 (1_A), D027.1 (1_A), D028.1 (1_A), D029.1 (1_A), D030.1 (1_A), D031.1 (1_A), D032.1 (1_A), D033.1 (1_A), D034.1 (1_A), D035.1 (1_A), D036.1 (1_A), D037.1 (1_A), D038.1 (1_A), D039.1 (1_A), D040.1 (1_A), D041.1 (1_A), D042.1 (1_A), D043.1 (1_A), D044.1 (1_A), D045.1 (1_A), D046.1 (1_A), D047.1 (1_A), D048.1 (1_A), D049.1 (1_A), D050.1 (1_A), D051.1 (1_A), D052.1 (1_A), D053.1 (1_A), D054.1 (1_A), D055.1 (1_A), D056.1 (1_A), D057.1 (1_A), D058.1 (1_A), D059.1 (1_A), D060.1 (1_A), D061.1 (1_A), D062.1 (1_A), FB1.1, J7.4 (VDD), J13.5, J13.5-5 (5), J101.1 (D), P13.P$1, P19.P$1, P24.P$1, Q5.1 (G), Q6.1 (G), Q7.2 (2_S), Q106.1 (G), Q107.1 (G), Q405.1 (G), R28.2, R30.1, R58.1, R95.2, R97.1, R98.1, R100.1, R103.1, R104.1, R109.1, R113.2, R115.1, R121.1, R122.1, R123.2, R127.2, R128.2, R129.2, R130.2, R131.2, R140.1, R141.1, R144.1, R149.1, R161.2, R177.2, R178.2, R200.1, R207.1, R208.1, R224.1, R237.2, R311.2, R422.2, R639.1, U5.1 (VCC), U6.5 (VDDIO), U6.8 (VDD), U7.1 (VCC), U9.6 (VDD), U10.6 (VDD), U12.7 (VCC), U12.10 (V3), U19.14 (14_VCC), U101.11 (VDD), U121.1 (VCC), U123.5 (VCC), U$196.1 (VCC)
VDD_5V: C10.2, C52.2, C82.1, C83.2, C86.1, C87.1, C90.1, C91.1, C117.2, C118.2, D021.+, D130.1 (1_A), FB9.2, J10.2, J14.P$4 (4VCC), J18.2, J19.2, L3.2, L4.1, L5.1, L7.1, R35.2, R90.2, R92.1, R93.1, R96.1, R99.1, R101.1, R102.1, R164.1, R165.1, R223.1, R257.1, R259.1, R289.1, SW1.3 (3_2A), U11.6 (6-VIN), U15.1 (VIN), U16.5 (5_IN), U18.4 (EN), U18.5 (IN)
VDD_5V2: C114.2, C195.1, D066.-, P62.P$1, R209.2, R284.2, U44.5 (5_VIN)
VDD_ESP32: R18.2, R30.2, R43.2, R46.2, R47.2, R52.2, R94.1
VDD_ESP32_1: R16.2, R36.2, R41.2, R42.2, R45.2, R53.2, R54.2, R140.2
VDD_FLASH: C20.1, IC1.8 (VCC), R38.2, R39.2
VDD_HP_0: C36.1, C37.2, R48.1, U1.26 (VDD_HP_0)
VDD_HP_2: C38.1, R49.1, U1.76 (VDD_HP_2)
VDD_HP_3: C39.1, R50.1, U1.91 (VDD_HP_3)
VDD_IO: C57.2, C58.2, R60.1, U4.13 (VDD_IO)
VDD_MIPI_DPHY: C40.1, C41.1, C42.1, R51.1, U1.41 (VDD_MIPI_DPHY)
XIN: C53.1, U4.3 (X2), Y2.1 (XIN)
XOUT: C54.2, U4.2 (X1), Y2.3 (XOUT)
XTAL_N: C7.2, U1.99 (XTAL_N), Y1.3 (CRYSTAL_2)
XTAL_P: C4.1, U1.100 (XTAL_P), Y1.1 (CRYSTAL_1)

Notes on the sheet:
I=6.8/R
Limit current 520mA
ESP32-P4
USB_TypeC *2 & TypeA
DC-DC:5V to 3V3
DC-DC:3V3 to 1V2
ESP32-P4_POWER
USB to UART
POWER
PHY
TypeA Limit Current
Relay
Ultrasonic Sensor
LIGHT SENSOR
I2C
ADD:0X5C
2.7V-4.2V
ADDRESS:0x5C
ADDRESS:1011100
LED
Temperature & Humidity(DHT20)
3V-5.5V
ADDRESS:0X38
PIR
Servo Motor
Accelerometer & Gyro
ADD:0X6B
HALL SENSOR
Custom_key
TTP223
Touch Sensor
GAS-MQ2
开关控制热释电功能的开启或关闭
SD card
MIC
Audio_Interface
CSI_Interface
I led=200mV/1.1=182mA
DSI_LED Driver
LDO:5V/3.3V to 1V8

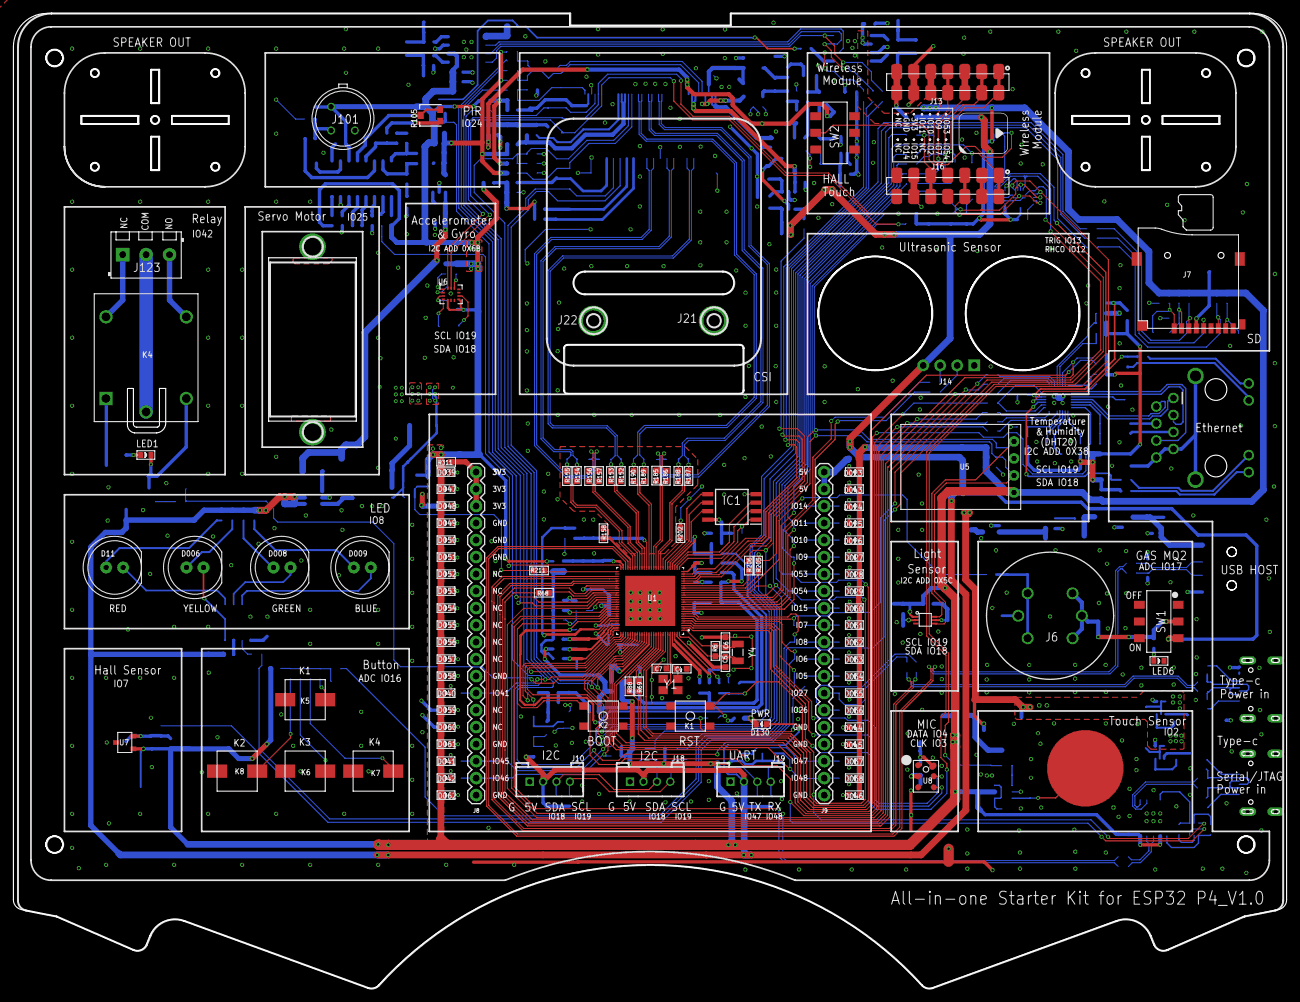
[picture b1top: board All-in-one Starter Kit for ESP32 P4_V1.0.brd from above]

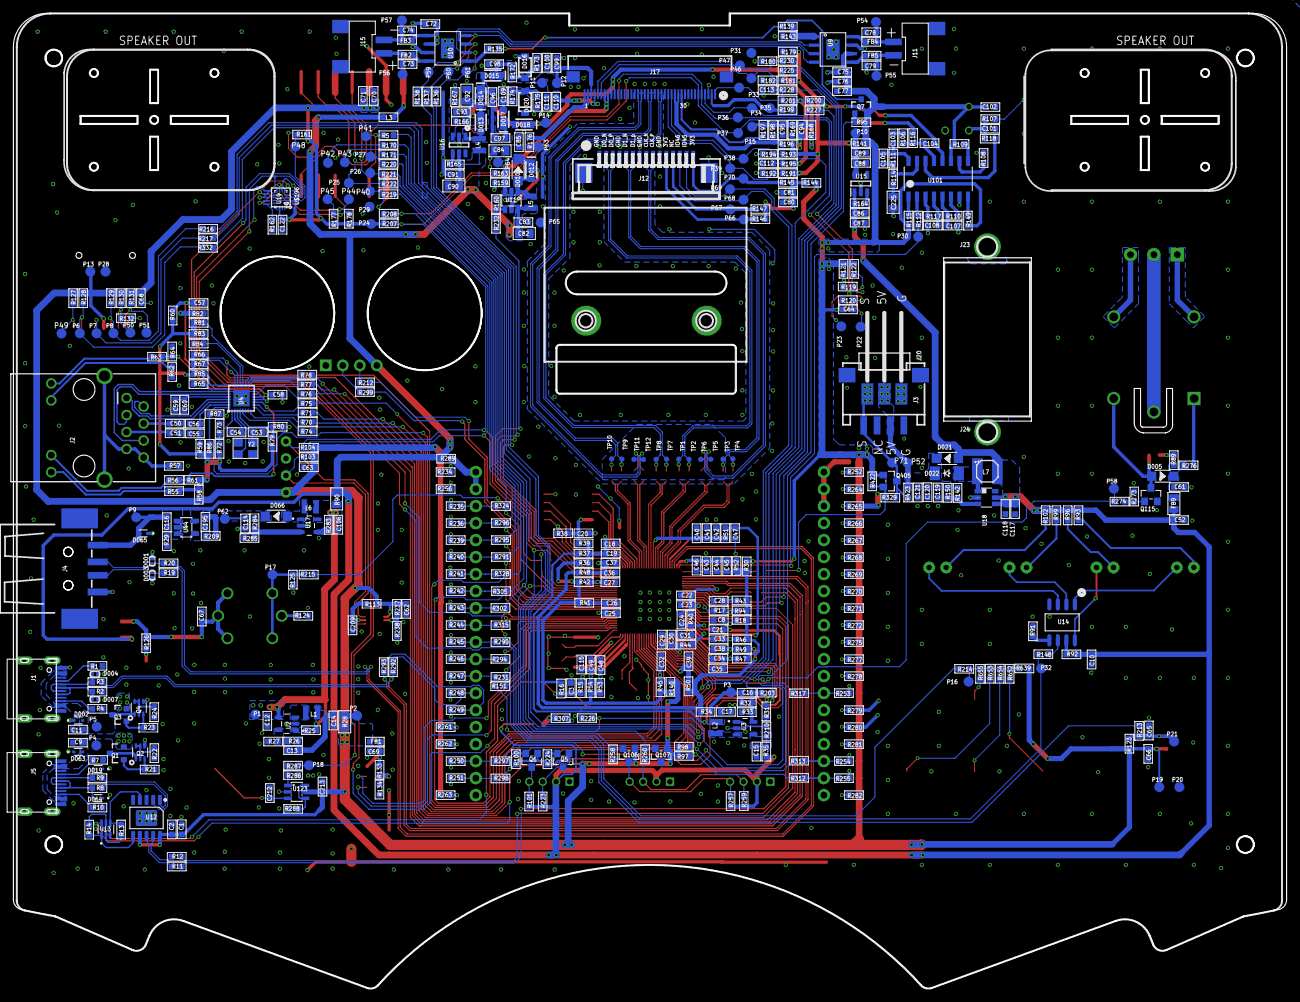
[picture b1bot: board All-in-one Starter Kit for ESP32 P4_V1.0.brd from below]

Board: 2 copper layers, 190.2 x 145.7 mm, 678 parts (571 on the bottom side), 399 nets.

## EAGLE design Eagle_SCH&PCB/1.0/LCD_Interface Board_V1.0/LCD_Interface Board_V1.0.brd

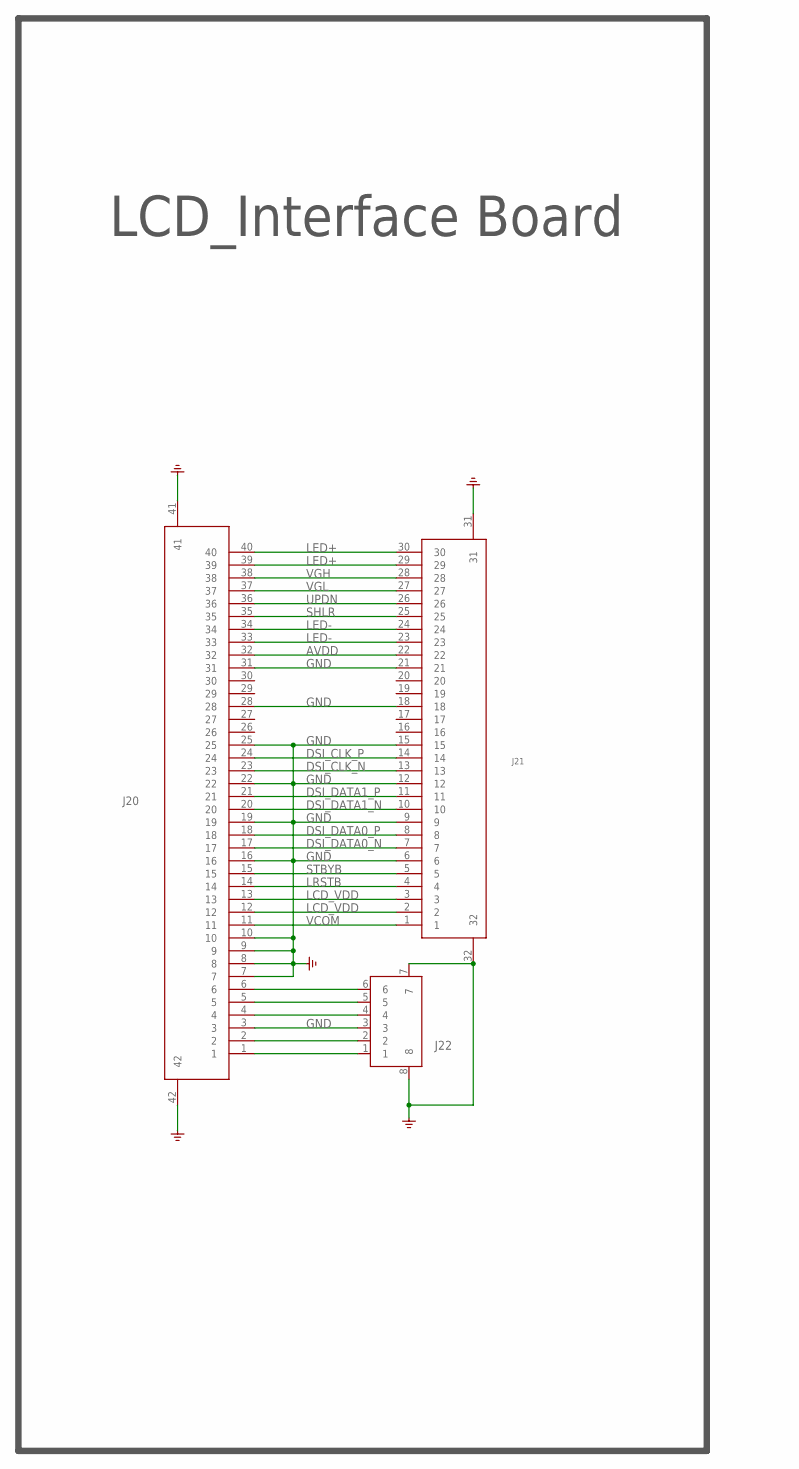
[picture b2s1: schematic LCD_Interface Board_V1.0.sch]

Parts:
J20: C19273935_40P_0.5MM_下接_HC-FPC-0.5-40P-FH20
J21: C23398852_30P_0.5MM_下接_FC-05A30P11H20
J22: C2856814_6P_0.5MM_下接_FPC-05F-6PH15

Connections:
AVDD: J20.32, J21.22
DSI_CLK_N: J20.23, J21.13
DSI_CLK_P: J20.24, J21.14
DSI_DATA0_N: J20.17, J21.7
DSI_DATA0_P: J20.18, J21.8
DSI_DATA1_N: J20.20, J21.10
DSI_DATA1_P: J20.21, J21.11
GND: J20.3, J20.7, J20.8, J20.9, J20.10, J20.16, J20.19, J20.22, J20.25, J20.28, J20.31, J20.41, J20.42, J21.6, J21.9, J21.12, J21.15, J21.18, J21.21, J21.31, J21.32, J22.3, J22.7, J22.8
LCD_VDD: J20.12, J20.13, J21.2, J21.3
LED+: J20.39, J20.40, J21.29, J21.30
LED-: J20.33, J20.34, J21.23, J21.24
LRSTB: J20.14, J21.4
unnamed: J20.6, J22.6
unnamed: J20.5, J22.5
unnamed: J20.4, J22.4
unnamed: J20.2, J22.2
unnamed: J20.1, J22.1
SHLR: J20.35, J21.25
STBYB: J20.15, J21.5
UPDN: J20.36, J21.26
VCOM: J20.11, J21.1
VGH: J20.38, J21.28
VGL: J20.37, J21.27

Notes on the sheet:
LCD_Interface Board

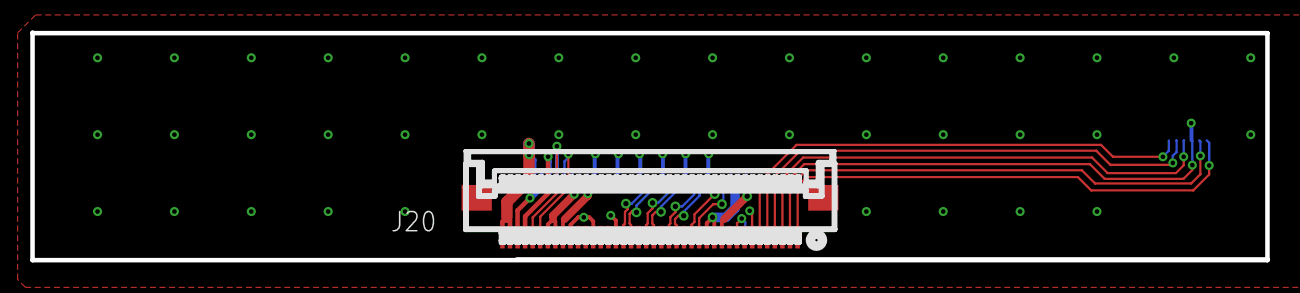
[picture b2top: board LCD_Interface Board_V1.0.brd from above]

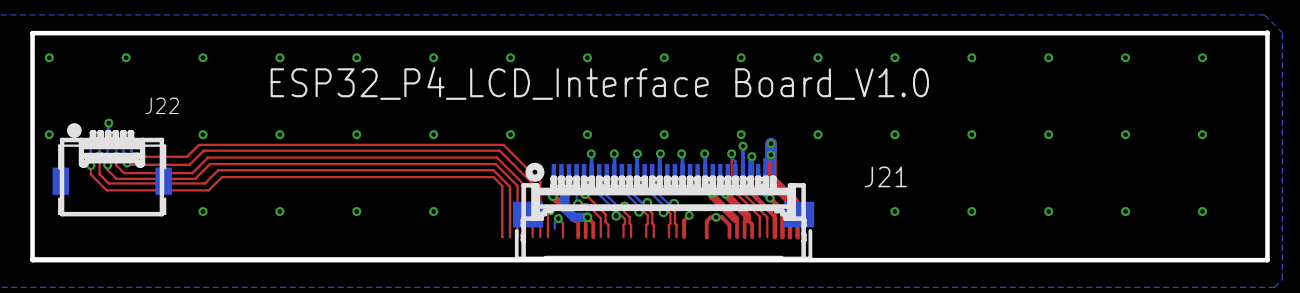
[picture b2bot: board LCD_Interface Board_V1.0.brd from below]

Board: 2 copper layers, 81.6 x 15.0 mm, 3 parts (2 on the bottom side), 23 nets.

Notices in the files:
parts and their libraries:
SparkFun-Coils: Licensing: Creative Commons ShareAlike 4.0 International - https://creativecommons.org/licenses/by-sa/4.0
